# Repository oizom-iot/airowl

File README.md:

<div align="center">

# **AIROWL**

The OIZOM Airowl is an indoor Air Quality Measurement device comprising of the ESP32 S3 powered M5stack Core S3 SE, which integrates the aforementioned controller chip, with a 320 x 240 LCD screen supporting capacitive touch, along with a speaker and the AXP2101 power management chip.

</div>

This Repository serves as the source of the complete Airowl, consisting of its Firmware source files, 3D files and PCB design Files.

This file provides instructions to assemble the individual components of the Airowl, along with its Bill of Materials (BOM).

The BOM for the Airowl is as Follows:

| SR. | ITEM DESCRIPTION       | NOTES                                  | Qty | Product Links                                                 |
|-----|------------------------|----------------------------------------|-----|---------------------------------------------------------------|
| 1   | M5 STACK              | SCREEN                                 | 1   | <a href="https://shop.m5stack.com/products/m5stack-cores3-se-iot-controller-w-o-battery-bottom" target="_blank">Link</a> |
| 2   | FRONT FACIA      | UV FRONT 1.3 MM + REAR BLACK 5 MM      | 1   | [Front](/Designfiles/Frontfacia)                                             |
| 3   | 3D PRINT BACK CASE    | BLACK MATTLE 3D PRINTED CASE           | 1   | [Back](/Designfiles/Backcover)                                          |
| 4   | FASTENERS             | M3 X 8 mm PHILIPS HEAD (SS)            | 2   |                                                               |
| 5   | FASTENERS             | M3 X 20 mm CSK Blunted (SS)            | 2   |                                                               |
| 6   | FASTENERS             | M3 X 25 mm CSK Blunted (SS)            | 2   |                                                               |
| 7   | Screw Driver (+)      | Mini Screw Driver                      | 1   |                                                               |
| 8   | TYPE C - TYPE C CABLE | PORTRONICS TYPE C CABLE                | 1   |                                                               |

More details of the individual components can be found as followed:

[PCB files](/Mountingboard/)

[Firmware](/Firmware)

[Squareline studio project files](/squareline/) 

[Design Files](/Designfiles/)

## Assembling the Airowl

The following is a cross sectional view of the Airowl dpicting its individual components and the way that they must be connected:

From left to right, we can observe the parts as follows:

1. Screws
2. [3D printed Black Case](Images/16.png)
3. [Printed circuit Board](Images/19.png)
4. M5 stack Core S3 SE
5. Sensirion SEN 54 sensor
6. [Front Cover](Images/15.png)

Ensure that the screws are connected correctly as depicted in the above picture, incase the screws are connected incorrectly, the longer screws might damage the physical cover of the Airowl.

On assembling the Airowl, it appears like depicted below:

On following the instructions in [Firmware](/Firmware/), the Airowl can be programmed succesfully.

Check this repository releases for newer firmware updates.

## Made by the Community, with -❤️-:

## Licensing

Airowl is available under MIT License

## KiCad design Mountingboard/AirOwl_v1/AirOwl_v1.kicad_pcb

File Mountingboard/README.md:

# Open Source PCB Design for M5Stack and Sensirion Dust Sensor SN54

This repository contains the open-source PCB design created using **KiCAD** software. The design includes both the schematic and the PCB layout.

---

## Table of Contents
- [Project Overview](#project-overview)
- [Key Features](#key-features)
- [Schematic and PCB Design](#schematic-and-pcb-design)
  - [Schematic](#schematic)
  - [Rendered PCB Images](#rendered-pcb-images)
- [Bill of Materials (BOM)](#bill-of-materials-bom)
- [How to Use](#how-to-use)
- [Contributing](#contributing)
- [License](#license)

---

## Project Overview

This PCB design integrates the **M5Stack** and the **Sensirion Dust Sensor SN54**, which measures the following parameters:

- **PM1**
- **PM2.5**
- **PM10**
- **Temperature**
- **Humidity**
- **TVOC Index**

The design facilitates I2C communication between the M5Stack and the dust sensor, with electrical connections labeled and organized for simplicity.

### Key Features

- **I2C Communication**: The M5Stack communicates with the Sensirion Dust Sensor via I2C.
- **Type-C Power Supply**: The entire PCB is powered through a Type-C connector.
- **Sensor Connections**: The wires from the sensor are soldered onto the PCB, with labeled footprints for I2C and 5V power connections.

---

## Schematic and PCB Design

The repository includes:

- **Schematic**: Showing the connection between M5Stack and Sensirion Dust Sensor SN54.
- **PCB Design**: Footprint and layout for soldering sensor wires and powering the device.

### Schematic

<details>
  <summary>Click to expand Schematic image</summary>

</details>

### Rendered PCB Images

- **Front View**

- **Back View**

---

## Interactive BOM

You can download the Interactive BOM [here](AirOwl_v1/bom/ibom.html).

> **Note**: Right-click the link and select "Open Link in New Tab" or press `Ctrl + Click` to open in a new tab.

## Bill of Materials (BOM)

| Part Name                   | Quantity | Reference Link |
|-----------------------------|----------|-----------|
| **M5Stack CoreS3-SE**        | 1        |   <a href="https://shop.m5stack.com/products/m5stack-cores3-se-iot-controller-w-o-battery-bottom" target="_blank">Link</a>        |
| **Sensirion Dust Sensor SEN54**| 1        |  <a href="https://www.digikey.in/en/products/detail/sensirion-ag/SEN54-SDN-T/15903868?s=N4IgTCBcDaIAQGUCiA5ArAFgLQICIqwBUQBdAXyA" target="_blank">Link</a> |          
| **Type-C Connector**         | 1        |  <a href="https://www.digikey.in/en/products/detail/same-sky/UJC-VP-3-SMT-TR/14310522?cur=INR&lang=en&utm_adgroup=&utm_source=google&utm_medium=cpc&utm_campaign=PMax%20Shopping_Product_High%20ROAS&utm_term=&productid=14310522&utm_content=&utm_id=go_cmp-20122528480_adg-_ad-__dev-c_ext-_prd-14310522_sig-CjwKCAjwmaO4BhAhEiwA5p4YL3F-XqxnqejDD6ez2iOCmQ-_p37bMZnp_VDgZ_CJA0CgT0X3qvwMexoCO9gQAvD_BwE&gad_source=1&gclid=CjwKCAjwmaO4BhAhEiwA5p4YL3F-XqxnqejDD6ez2iOCmQ-_p37bMZnp_VDgZ_CJA0CgT0X3qvwMexoCO9gQAvD_BwE">Link</a>         |                       
| **I2C Pull-up Resistors [R1, R2]**    | 2        | 10K 0805 (Optional)          |                                 
| **Resistors [R3, R4]**                | 2        | 4.7K 0805 (Must for Type C PD)         |         
| **Male Header Pin**                | 1        | 2.54mm 40x2 Male Header Pin         |             
| **Sensirion Dust Sensor Cable**                | 1       | <a href="https://evelta.com/jst-ghr-06v-cable-6pin-1-25mm-pitch-female-connector-15cm/" target="_blank">Link</a>         |             

> **Note:** This table will be updated with detailed part information.

---

## How to Use

To get started with this PCB design:

```bash
# Step 1: Clone the repository
git clone https://github.com/your-repo-name.git

# Step 2: Open the project in KiCAD

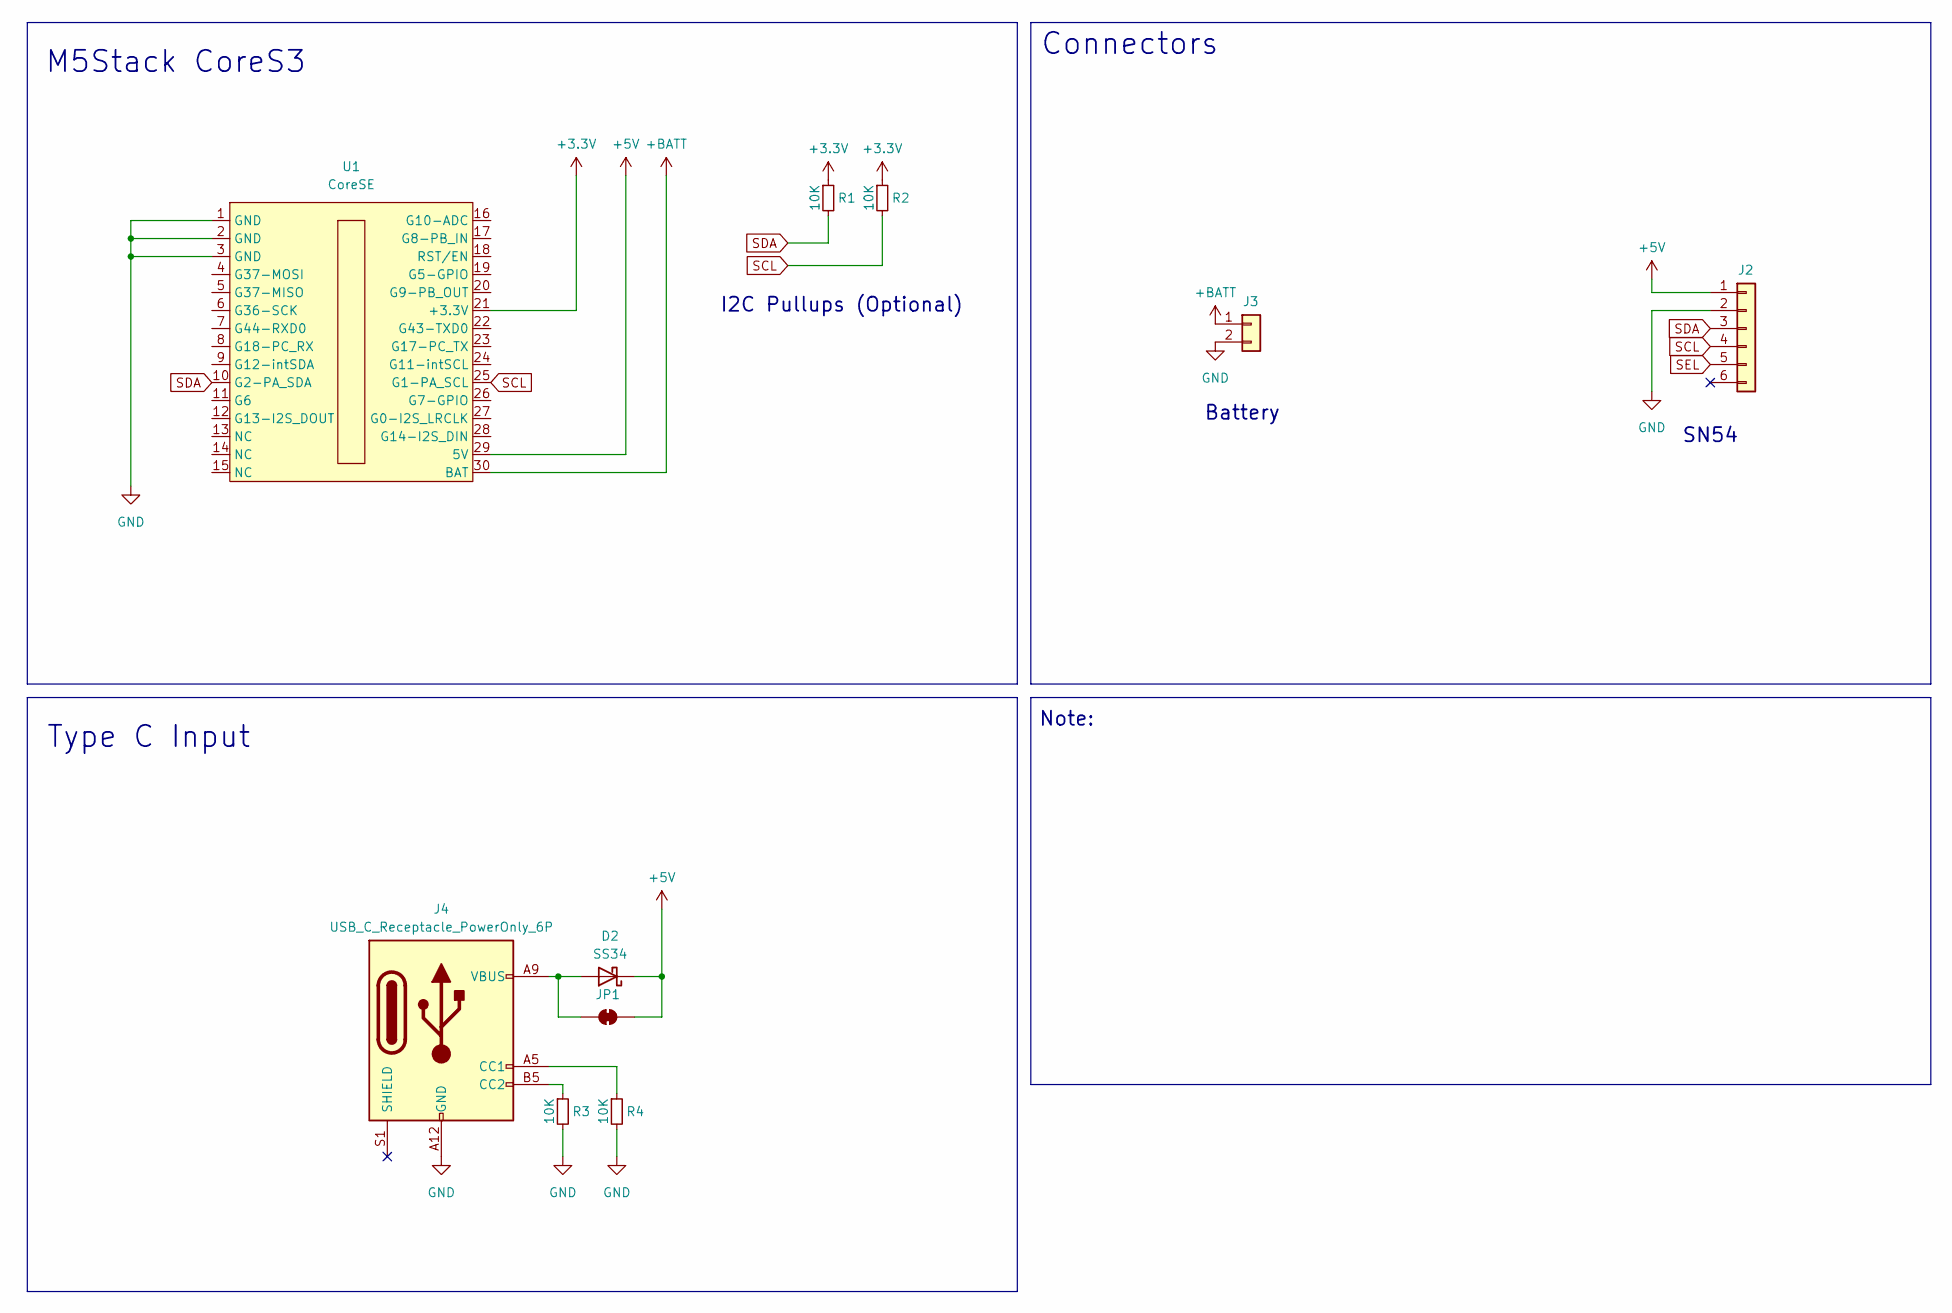
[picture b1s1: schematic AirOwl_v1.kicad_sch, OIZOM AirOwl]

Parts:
D2: SS34; D_SMA
J2: Conn_01x06; PinHeader_1x06_P2.54mm_Vertical
J3: Conn_01x02; JST_PH_B2B-PH-K_1x02_P2.00mm_Vertical
J4: USB_C_Receptacle_PowerOnly_6P; MOLEX_2171780001
JP1: SolderJumper_2_Bridged; SolderJumper-2_P1.3mm_Bridged_RoundedPad1.0x1.5mm
R1, R2, R3, R4: 10K; R_0805_2012Metric_Pad1.20x1.40mm_HandSolder
U1: CoreSE; CoreS3

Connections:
+3.3V: R1.1, R2.1, U1.21 (+3.3V)
+5V: D2.1 (K), J2.1, JP1.2 (B), U1.29 (5V)
+BATT: J3.1, U1.30 (BAT)
GND: J2.2, J3.2, J4.A12 (GND), J4.B12 (GND), R3.2, R4.2, U1.1 (GND), U1.2 (GND), U1.3 (GND)
unnamed: D2.2 (A), J4.A9 (VBUS), J4.B9 (VBUS), JP1.1 (A)
unnamed: J4.A5 (CC1), R4.1
unnamed: J4.B5 (CC2), R3.1
SCL: J2.4, R2.2, U1.25 (G1-PA_SCL)
SDA: J2.3, R1.2, U1.10 (G2-PA_SDA)
SEL: J2.5

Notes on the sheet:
Battery
I2C Pullups (Optional)
M5Stack CoreS3
Type C Input
Connectors
SN54
Note:

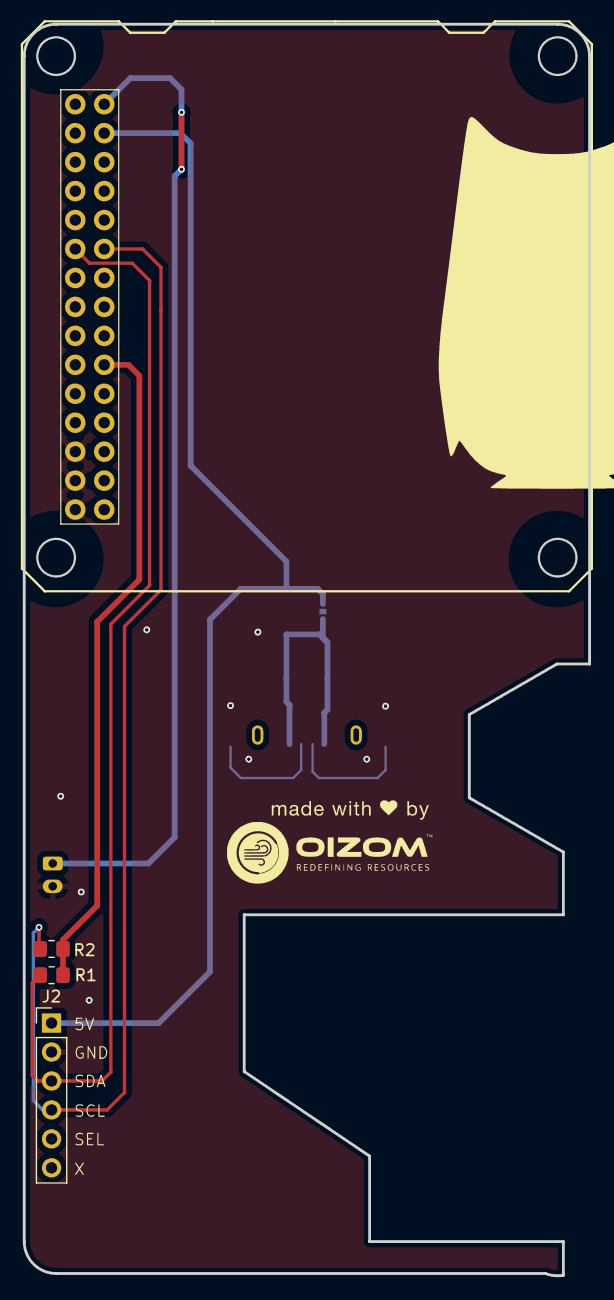
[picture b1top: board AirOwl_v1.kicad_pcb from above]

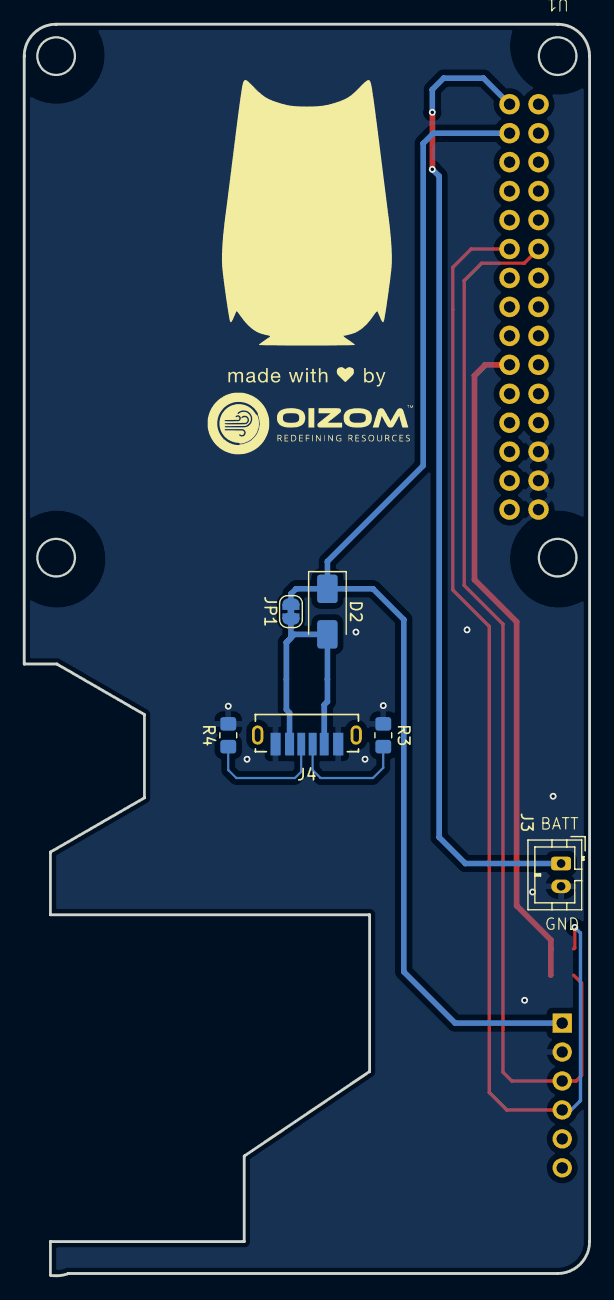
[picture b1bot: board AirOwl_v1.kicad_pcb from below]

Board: 2 copper layers, 49.6 x 109.8 mm, 10 parts (7 on the bottom side), 9 nets.

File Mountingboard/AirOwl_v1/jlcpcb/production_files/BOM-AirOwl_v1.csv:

Comment,Designator,Footprint,LCSC
10K,R2,R_0805_2012Metric_Pad1.20x1.40mm_HandSolder,
10K,R1,R_0805_2012Metric_Pad1.20x1.40mm_HandSolder,
Conn_01x06,J2,PinHeader_1x06_P2.54mm_Vertical,
USB_C_Receptacle_PowerOnly_6P,J4,MOLEX_2171780001,
USB_C_Receptacle_PowerOnly_6P,J1,USB-C_6P_Vertical_THT,
SS34,D2,D_SMA,
CoreSE,U1,CoreS3,
Conn_01x02,J3,JST_PH_B2B-PH-K_1x02_P2.00mm_Vertical,

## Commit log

2024-09-18 Commit done
2024-09-18 final commit with RS
2024-09-19 squareline project commited
2024-09-19 UI updated
    UI updated
2024-09-20 UI updated and labels, chart values are modified.
    UI updated,
    Pm1.h file created, to drive values of parameters into labels on the screen.
    Sensor data to be fed into this file.
    uiscreen files can be used to overwrite the static values of the graph defined in squareline studio.
2024-09-24 ui updated
2024-09-24 Commited basic updated code
2024-09-24 squareline project updated
2024-09-24 Commited final code
2024-09-24 Final commit with all the changes
2024-09-25 Final code
2024-09-25 Final with timesync
2024-09-25 Studio updated
2024-09-25 minor bug fix
2024-09-25 max buf resolved
2024-09-27 Final commit
2024-09-27 Interval updated to 5 minute
2024-09-27 bug resolved
2024-10-01 Airowl Folder structure
2024-10-01 Commited Readme files
2024-10-01 Images added
2024-10-02 images updated
2024-10-02 Added functionality of QR Code screen
2024-10-02 firmware.md uploaded
2024-10-02 image issue resolved
2024-10-02 image issue corrected
    / removed from image paths
2024-10-02 README.md replaced with firmware.md
2024-10-02 images moved to md_images folder
2024-10-02 new images and logo commited
2024-10-02 KiCAD Project File
2024-10-02 Create 3d files
2024-10-04 Firmware version added
2024-10-04 Air owl 3D files
2024-10-04 Readme.md updated
    Initial Readme.md updated
2024-10-07 BOM Added
2024-10-07 Data Frequency updated
2024-10-07 design files updated
2024-10-07 2design folders created
2024-10-07 Readme updated in design folder
2024-10-07 Design files, readme updated with images
2024-10-08 Updated Folders
2024-10-10 Create LICENSE
2024-10-10 gif added
2024-10-10 Firmware folder clear
2024-10-10 removed
2024-10-11 PCB renders
2024-10-11 Update README.md | Mounting Board
2024-10-11 ibom.html added
2024-10-11 GIF file
2024-10-13 GIF commited
2024-10-24 ConnectAndFirmwareUpdate
2024-10-24 Firmware Update and Wifi Connection Video
2024-11-06 Update ui.c
    updated ui.c file to fix position of pupils on owl screen
2024-12-02 Update ui_dashboard.c
    changed PPB label on dashboard screen to "Index"
2025-01-06 Wifi Qr code updated
2025-02-13 Smart QR Code generator

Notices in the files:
Mountingboard/README.md:
License: MIT
